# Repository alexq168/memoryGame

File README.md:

# memoryGame

A memory game made for pathfinder

## Pathfinder Session 1 - [40 minutes]

What I did:

I downloaded KiCad and started following the tutorial on (pathfinder.hackclub.com)

## Pathfinder Session 2 - [30 minutes]

What I did:

I finished my schematic and started working on the design of the PCB.

## Pathfinder Session 3 - [1 hour] 

I finished my design of the circuit board and wired it all up.

## Pathfinder Session 4 - [20 minutes]

What I did:

I added the 3d models to the circuit board, and added the keyswitch to the buttons.

## Pathfinder Session 5 - [20 minutes]

What I did:

I added the rest of the 3d models, which were the Cherry MX keycap and the 5mm LED.

## Pathfinder Session 6 - [2 hours]

What I did:

I attempted to code the memory game but failed, and settled on the base for the game with a random sequence of 3 LEDS flashing, in total, 5 times. I can expand on the code, but do not know how to at this current moment.

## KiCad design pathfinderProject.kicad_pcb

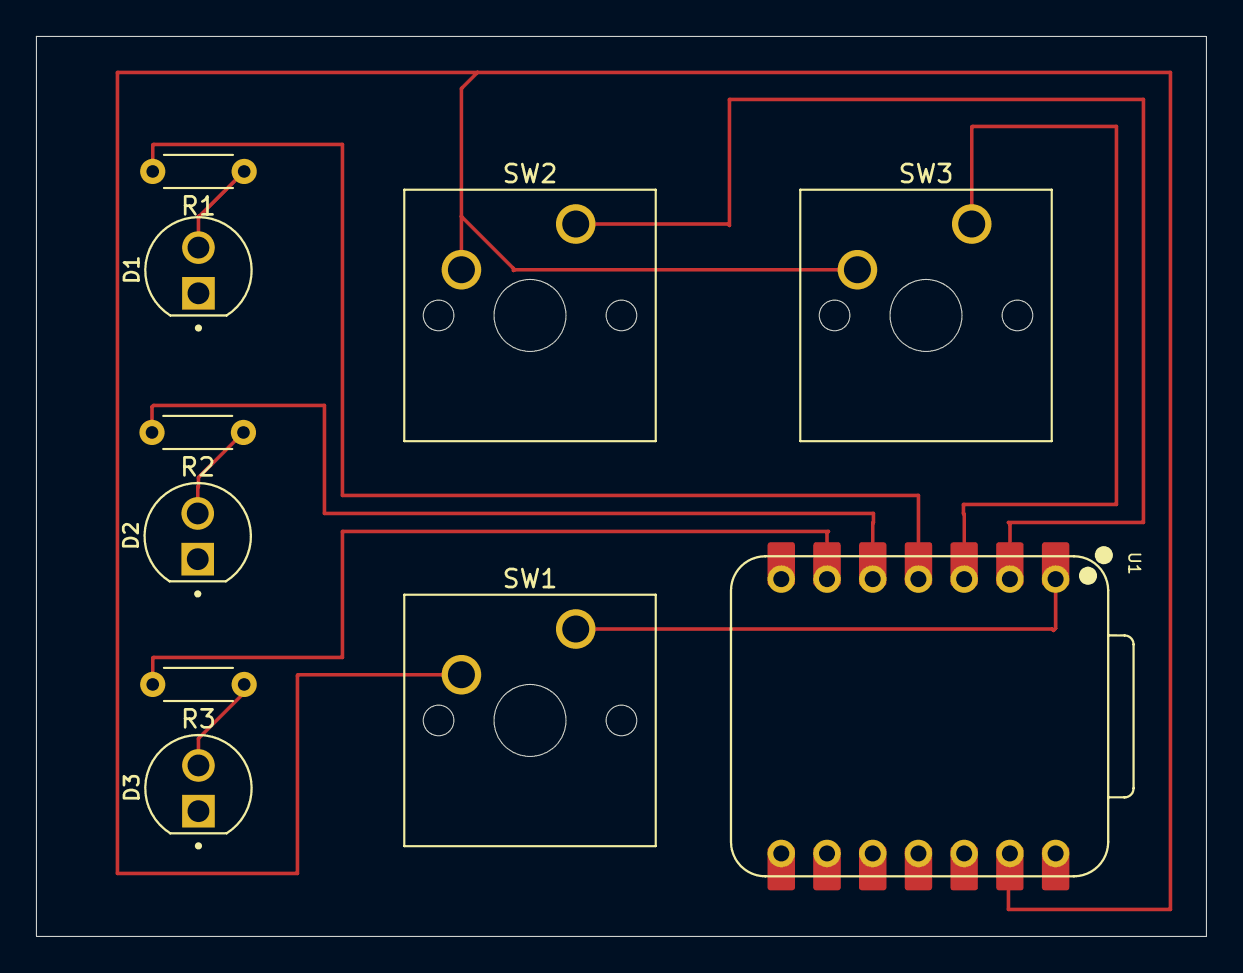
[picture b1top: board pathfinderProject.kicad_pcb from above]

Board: 2 copper layers, 65.0 x 50.0 mm, 10 parts (0 on the bottom side), 10 nets.

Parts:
D1, D2, D3: L08R5000Q1; LEDRD254W57D500H1070
R1, R2, R3: R; R_Axial_DIN0204_L3.6mm_D1.6mm_P5.08mm_Horizontal
SW1, SW2, SW3: SW_Push; SW_Cherry_MX_1.00u_PCB
U1: XIAO-RP2040-DIP

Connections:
GND: SW1.2, SW2.2, SW3.2, U1.13 (GND)
LED1: R1.2, U1.4 (GPIO29/ADC3/A3)
LED2: R2.2, U1.5 (GPIO6/SDA)
LED3: R3.2, U1.6 (GPIO7/SCL)
unnamed: D1.A, R1.1
unnamed: D2.A, R2.1
unnamed: D3.A, R3.1
button1: SW1.1, U1.1 (GPIO26/ADC0/A0)
button2: SW2.1, U1.2 (GPIO27/ADC1/A1)
button3: SW3.1, U1.3 (GPIO28/ADC2/A2)

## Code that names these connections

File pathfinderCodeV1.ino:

int button1 = D0;
int button2 = D1;
int button3 = D2;

int LED1 = D3;
int LED2 = D4;
int LED3 = D5;

void setup() {
    pinMode(button1, INPUT_PULLUP);

pinMode(button2, INPUT_PULLUP);

pinMode(button3, INPUT_PULLUP);


pinMode(LED1, OUTPUT);

pinMode(LED2, OUTPUT);

pinMode(LED3, OUTPUT);

   int memNum1 = random(1, 3);
  int memNum2 = random(1, 3);
  int memNum3 = random(1, 3);
  int memNum4 = random(1, 3);
  int memNum5 = random(1, 3);

long startTime = millis();
}

void loop(){
  
if (memNum1 == 1){
  digitalWrite(LED1, HIGH);
  delay (500);
  digitalWrite(LED1, LOW);
} else {
  if (memNum1 == 2){
    digitalWrite(LED2 HIGH);
      delay (500);
    digitalWrite(LED2, LOW);
  } else {
    digitalWrite(LED3, HIGH);
      delay (500);
    digitalWrite(LED3, LOW);
  }
}

delay (500);

if (memNum2 == 1){
  digitalWrite(LED1, HIGH);
  delay (500);
  digitalWrite(LED1, LOW);
} else {
  if (memNum2 == 2){
    digitalWrite(LED2 HIGH);
      delay (500);
    digitalWrite(LED2, LOW);
  } else {
    digitalWrite(LED3, HIGH);
      delay (500);
    digitalWrite(LED3, LOW);
  }
}

delay (500);

if (memNum3 == 1){
  digitalWrite(LED1, HIGH);
  delay (500);
  digitalWrite(LED1, LOW);
} else {
  if (memNum3 == 2){
    digitalWrite(LED2 HIGH);
      delay (500);
    digitalWrite(LED2, LOW);
  } else {
    digitalWrite(LED3, HIGH);
      delay (500);
    digitalWrite(LED3, LOW);
  }
}

delay (500);

if (memNum4 == 1){
  digitalWrite(LED1, HIGH);
  delay (500);
  digitalWrite(LED1, LOW);
} else {
  if (memNum4 == 2){
    digitalWrite(LED2 HIGH);
      delay (500);
    digitalWrite(LED2, LOW);
  } else {
    digitalWrite(LED3, HIGH);
      delay (500);
    digitalWrite(LED3, LOW);
  }
}

delay (500);

if (memNum5 == 1){
  digitalWrite(LED1, HIGH);
  delay (500);
  digitalWrite(LED1, LOW);
} else {
  if (memNum5 == 2){
    digitalWrite(LED2 HIGH);
      delay (500);
    digitalWrite(LED2, LOW);
  } else {
    digitalWrite(LED3, HIGH);
      delay (500);
    digitalWrite(LED3, LOW);
  }
}

delay (500);
  
}
